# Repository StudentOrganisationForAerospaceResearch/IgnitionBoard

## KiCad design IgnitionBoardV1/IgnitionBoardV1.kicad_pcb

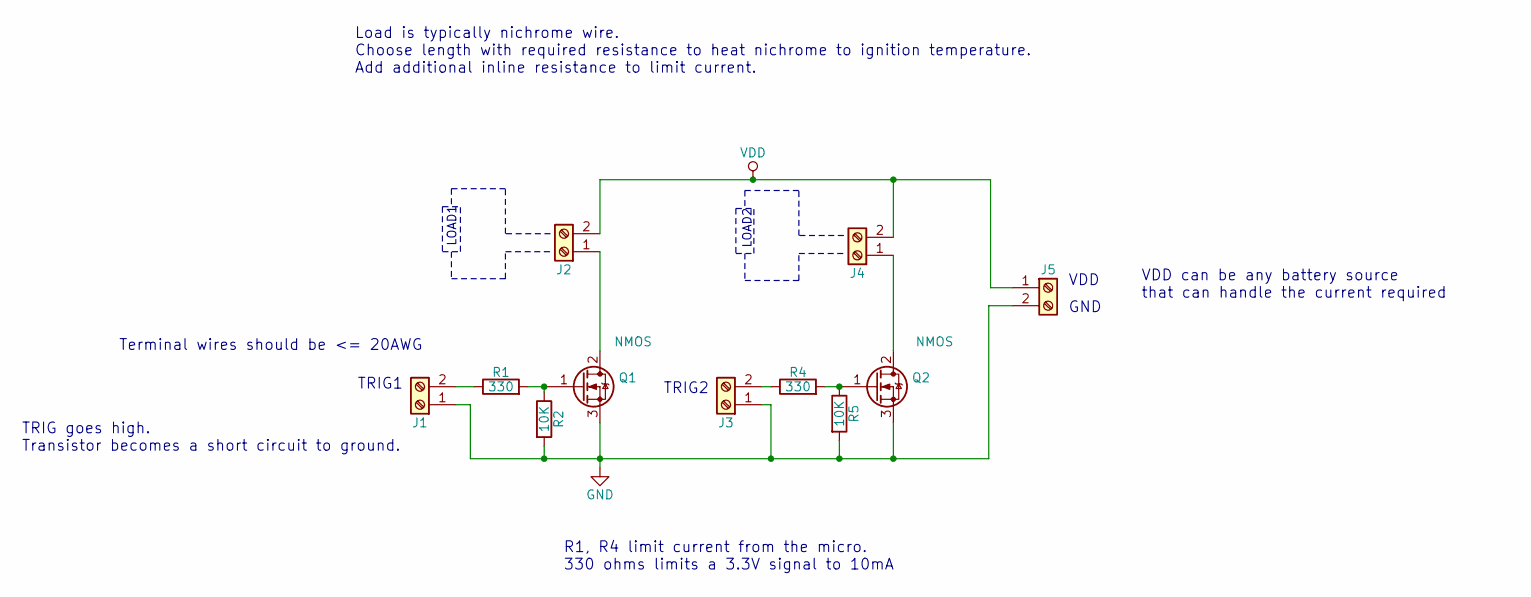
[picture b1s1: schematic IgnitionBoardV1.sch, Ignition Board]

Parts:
J1, J2, J3, J4, J5: Screw_Terminal_01x02; TerminalBlock_Phoenix_PT-1,5-2-5.0-H_1x02_P5.00mm_Horizontal
Q1, Q2: NMOS; TO-220-3_Vertical
R1, R4: 330; R_Axial_DIN0207_L6.3mm_D2.5mm_P10.16mm_Horizontal
R2, R5: 10K; R_Axial_DIN0207_L6.3mm_D2.5mm_P10.16mm_Horizontal

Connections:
GND: J1.1, J3.1, J5.2, Q1.3 (S), Q2.3 (S), R2.2, R5.2
unnamed: J1.2, R1.1
unnamed: J2.1, Q1.2 (D)
unnamed: J3.2, R4.1
unnamed: J4.1, Q2.2 (D)
unnamed: Q1.1 (G), R1.2, R2.1
unnamed: Q2.1 (G), R4.2, R5.1
VDD: J2.2, J4.2, J5.1

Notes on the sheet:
LOAD1
LOAD2
VDD
GND
TRIG1
TRIG2
Load is typically nichrome wire. Choose length with required resistance to heat nichrome to ignition temperature. Add additional inline resistance to limit current.
Terminal wires should be <= 20AWG
TRIG goes high. Transistor becomes a short circuit to ground.
R1, R4 limit current from the micro. 330 ohms limits a 3.3V signal to 10mA
VDD can be any battery source that can handle the current required

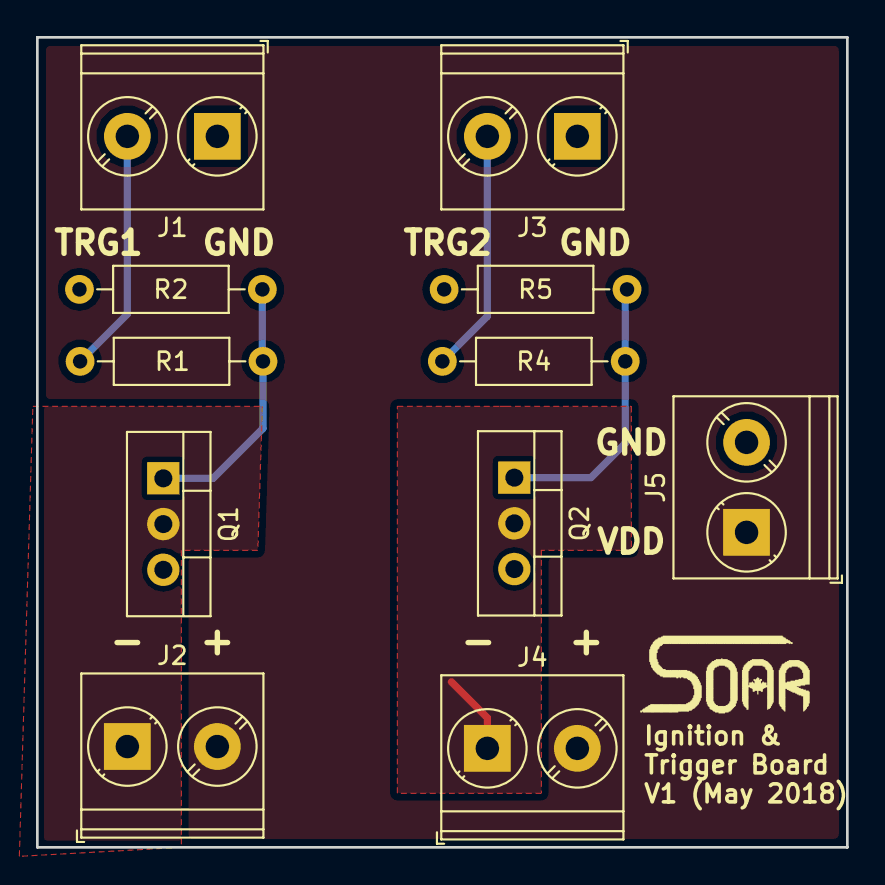
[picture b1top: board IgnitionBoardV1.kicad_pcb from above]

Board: 2 copper layers, 45.0 x 45.0 mm, 12 parts (0 on the bottom side), 8 nets.

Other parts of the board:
LOGO_SOAR: LOGO_SOAR

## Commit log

2018-02-24 Initial Commit of design files
2018-02-24 restructure directories
2018-03-27 increase copper pours around holes
2018-03-27 add reccomended parts in schematic
2018-03-31 Add board name and version to silkscreen
2018-05-17 Generated gerbers
